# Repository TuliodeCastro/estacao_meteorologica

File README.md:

# 🌦️ Estação Meteorológica com LoRa

Sistema de monitoramento climático distribuído usando **ESP8266, LoRa, Sensores** e **Firebase** para registro de dados em nuvem.

## 📋 Visão Geral

Um projeto de IoT que coleta dados meteorológicos (temperatura, pressão, umidade, vento, chuva, radiação solar) em um **nó sensor remoto** e os transmite via **LoRa** para um **gateway central**, que envia os dados para o **Firebase Realtime Database**.

### Arquitetura
```
Node Sensor (ESP8266)
  ├─ BME280 (temperatura, pressão, umidade)
  ├─ Anemômetro (velocidade do vento)
  ├─ Pluviômetro (medição de chuva)
  ├─ ADS1115 ADC (direção do vento, irradiância)
  └─ LoRa (transmissor)
          ↓ LoRa Transmission
        Gateway (ESP8266)
          ├─ LoRa (receptor)
          ├─ Wi-Fi
          └─ Firebase Client
                ↓
        📊 Firebase Realtime Database (Nuvem)
```

## 📁 Estrutura do Projeto

```
estacao_meteorologica/
├── README.md                          (este arquivo)
├── SETUP.md                           (instruções de configuração)
├── LICENSE                            (licença do projeto)
├── .gitignore                         (ignora arquivos sensíveis)
│
├── docs/
│   ├── HARDWARE.md                   (pinagem, componentes, esquemático)
│   ├── ARCHITECTURE.md               (fluxo de dados, protocolos)
│   └── DEPLOYMENT.md                 (guia de produção)
│
└── firmware/
    ├── README.md                     (documentação do firmware)
    ├── SECURITY_GUIDELINES.md        (boas práticas de segurança)
    │
    ├── gateway_lora/                 (receptor LoRa + Wi-Fi + Firebase)
    │   ├── src/main.cpp
    │   ├── include/credentials.h     (credenciais - NÃO COMMITAR)
    │   ├── include/credentials.h.example
    │   ├── SECURITY.md
    │   └── platformio.ini
    │
    └── node_sensor/                  (sensor remoto com LoRa)
        ├── src/main.cpp
        ├── include/
        ├── platformio.ini
        └── test/

```

## 🔧 Módulos

### Node Sensor (`firmware/node_sensor/`)
- **Placa:** D1 R2 Mini (ESP8266)
- **Sensores:**
  - BME280 (I2C): Temperatura, Pressão, Umidade
  - ADS1115 (I2C): Entrada analógica para piranômetro e direção
  - Anemômetro (GPIO): Sensor de efeito Hall
  - Pluviômetro (GPIO): Sensor de chuva
- **Ciclo:** Amostra a cada 5s por 2 min, transmite CSV via LoRa, dorme por 3 min

### Gateway LoRa (`firmware/gateway_lora/`)
- **Placa:** NodeMCU V2 (ESP8266)
- **Conectividade:**
  - LoRa (SoftwareSerial): Recebe dados do nó sensor
  - Wi-Fi: Conexão à rede local
  - Firebase: Envia dados para nuvem
- **Funcionalidade:** Recebe CSV do sensor, valida checksum, envia para Firebase

## 📊 Formato de Dados

**CSV transmitido pelo sensor:**
```
temp,pres,umid,pulsos,chuva,velMS,rajada,dir,irrad*CHECKSUM
25.5,1013.2,65.3,120,0.25,2.14,3.45,180,450.2*AB
```

| Campo | Descrição | Unidade |
|-------|-----------|---------|
| temp | Temperatura média | °C |
| pres | Pressão média | hPa |
| umid | Umidade relativa média | % |
| pulsos | Contagem de pulsos do vento | - |
| chuva | Acumulado de chuva | mm |
| velMS | Velocidade média do vento | m/s |
| rajada | Velocidade máxima (rajada) | m/s |
| dir | Direção média do vento | graus (0-360°) |
| irrad | Irradiância solar média | W/m² |

## 📚 Documentação

- **[SETUP.md](./SETUP.md)** — Como configurar e fazer upload do firmware
- **[docs/HARDWARE.md](./docs/HARDWARE.md)** — Pinagem, componentes, esquemático
- **[docs/ARCHITECTURE.md](./docs/ARCHITECTURE.md)** — Fluxo de dados e protocolos
- **[firmware/SECURITY_GUIDELINES.md](./firmware/SECURITY_GUIDELINES.md)** — Boas práticas de segurança
- **[firmware/gateway_lora/SECURITY.md](./firmware/gateway_lora/SECURITY.md)** — Configuração de credenciais

## 🛠️ Troubleshooting

### Sensor não transmite dados
1. Verifique conexão LoRa (pinos D6/D7)
2. Verifique sensor BME280 no Serial Monitor
3. Verifique poder do sensor (voltagem 3.3V)

### Gateway não recebe dados
1. Verifique Wi-Fi (Serial Monitor mostra IP?)
2. Verifique Firebase (credenciais corretas?)
3. Verifique potência LoRa (mesmos pinos)

### Firebase não recebe dados
1. Verifique credenciais em `credentials.h`
2. Verifique Firebase Rules permitem escrita anônima
3. Verifique conectividade Wi-Fi do gateway

Veja mais em **[docs/HARDWARE.md](./docs/HARDWARE.md)** e **[firmware/README.md](./firmware/README.md)**

## 📝 Licença

Este projeto está licenciado sob a [Licença MIT](./LICENSE).

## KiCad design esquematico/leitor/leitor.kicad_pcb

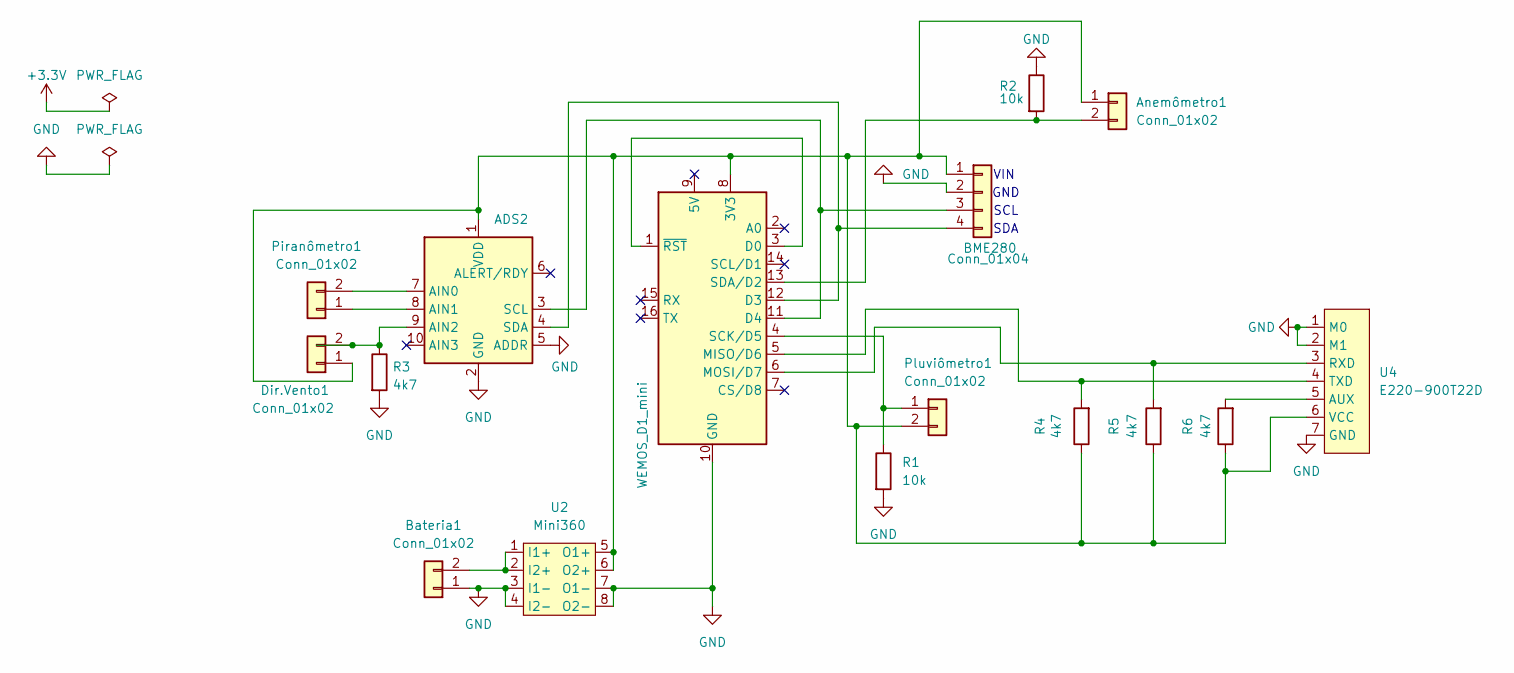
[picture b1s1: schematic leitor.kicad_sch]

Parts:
ADS2: ADS1115IDGS; ADS1115-VSSOP-28mmx17mm
Anemômetro1: Conn_01x02; TerminalBlock_CUI_TB007-508-02_1x02_P5.08mm_Horizontal
BME280: Conn_01x04; JST_XH_B4B-XH-A_1x04_P2.50mm_Vertical
Bateria1: Conn_01x02; TerminalBlock_CUI_TB007-508-02_1x02_P5.08mm_Horizontal
Dir.Vento1: Conn_01x02; TerminalBlock_CUI_TB007-508-02_1x02_P5.08mm_Horizontal
Piranômetro1: Conn_01x02; TerminalBlock_CUI_TB007-508-02_1x02_P5.08mm_Horizontal
Pluviômetro1: Conn_01x02; TerminalBlock_CUI_TB007-508-02_1x02_P5.08mm_Horizontal
R1, R2: 10k; R_Axial_DIN0207_L6.3mm_D2.5mm_P10.16mm_Horizontal
R3, R4, R5, R6: 4k7; R_Axial_DIN0207_L6.3mm_D2.5mm_P10.16mm_Horizontal
U1: WEMOS_D1_mini; WEMOS_D1_mini_light
U2: Mini360
U4: E220-900T22D

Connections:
GND: ADS2.2 (GND), ADS2.5 (ADDR), BME280.2, Bateria1.1, R1.2, R2.1, R3.2, U1.10 (GND), U2.3 (I1-), U2.4 (I2-), U2.7 (O1-), U2.8 (O2-), U4.1 (M0), U4.2 (M1), U4.7 (GND)
unnamed: ADS2.7 (AIN0), Piranômetro1.2
unnamed: ADS2.8 (AIN1), Piranômetro1.1
unnamed: ADS2.9 (AIN2), Dir.Vento1.2, R3.1
unnamed: ADS2.3 (SCL), BME280.3, U1.11 (D4)
unnamed: ADS2.4 (SDA), BME280.4, U1.12 (D3)
unnamed: ADS2.1 (VDD), Anemômetro1.1, BME280.1, Dir.Vento1.1, Pluviômetro1.2, R4.1, R5.1, R6.1, U1.8 (3V3), U2.5 (O1+), U2.6 (O2+), U4.6 (VCC)
unnamed: Anemômetro1.2, R2.2, U1.13 (SDA/D2)
unnamed: Bateria1.2, U2.1 (I1+), U2.2 (I2+)
unnamed: Pluviômetro1.1, R1.1, U1.4 (SCK/D5)
unnamed: U1.1 (~RST), U1.3 (D0)
unnamed: R4.2, U1.5 (MISO/D6), U4.4 (TXD)
unnamed: R5.2, U1.6 (MOSI/D7), U4.3 (RXD)
unnamed: R6.2, U4.5 (AUX)

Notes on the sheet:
VIN
GND
SCL
SDA

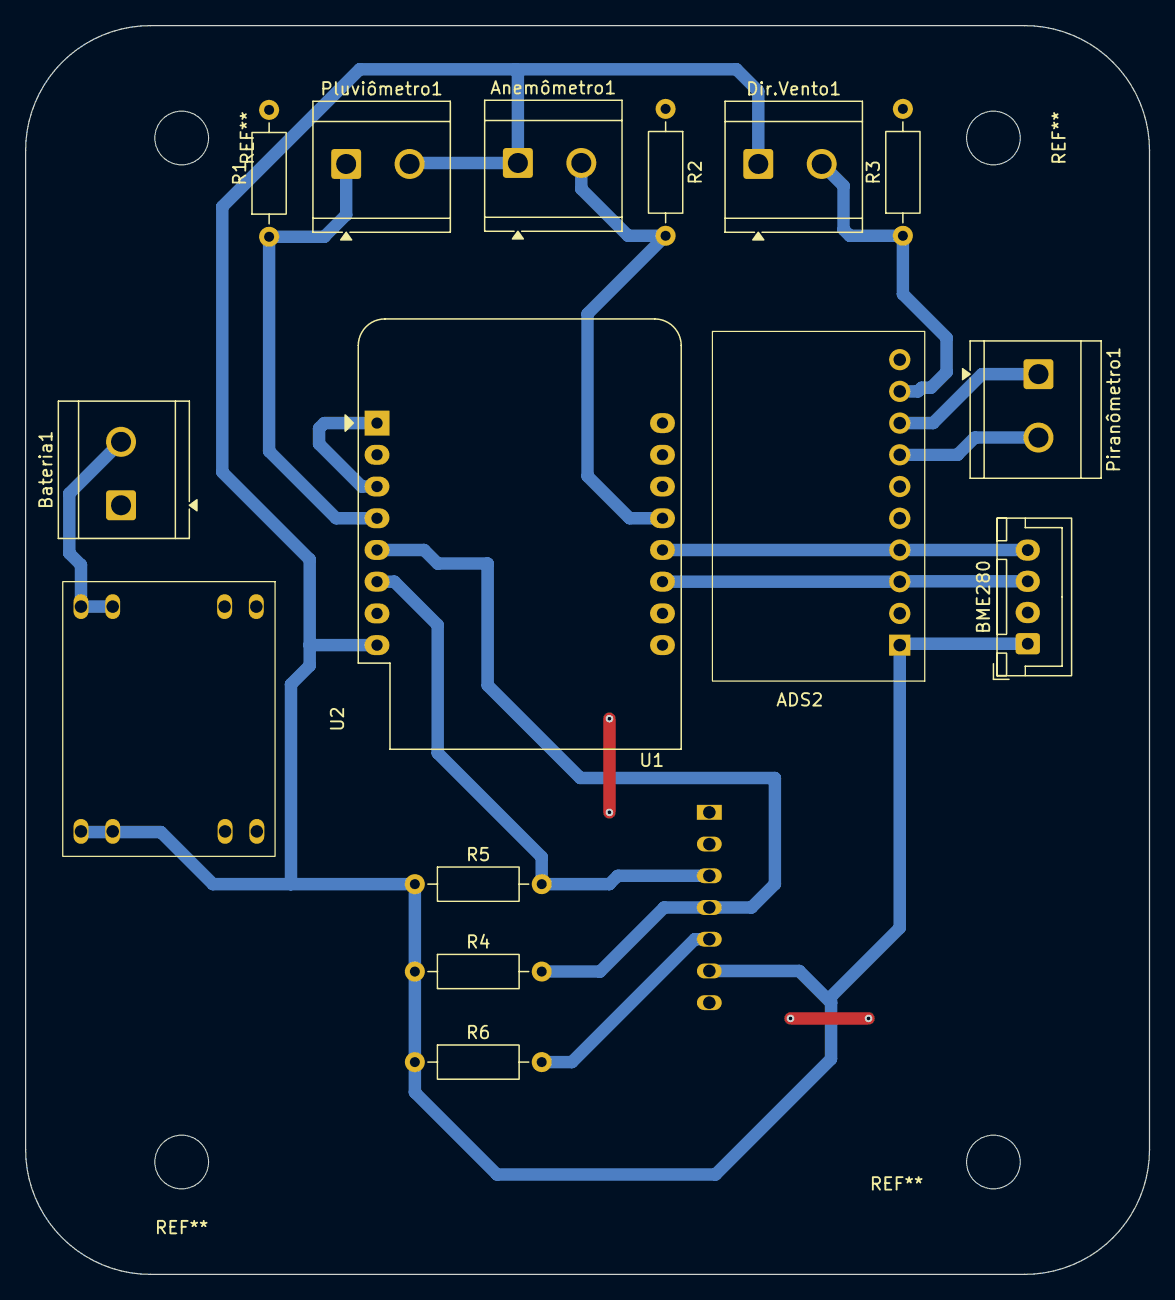
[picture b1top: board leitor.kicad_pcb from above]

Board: 2 copper layers, 90.0 x 100.0 mm, 16 parts (1 on the bottom side), 14 nets.
